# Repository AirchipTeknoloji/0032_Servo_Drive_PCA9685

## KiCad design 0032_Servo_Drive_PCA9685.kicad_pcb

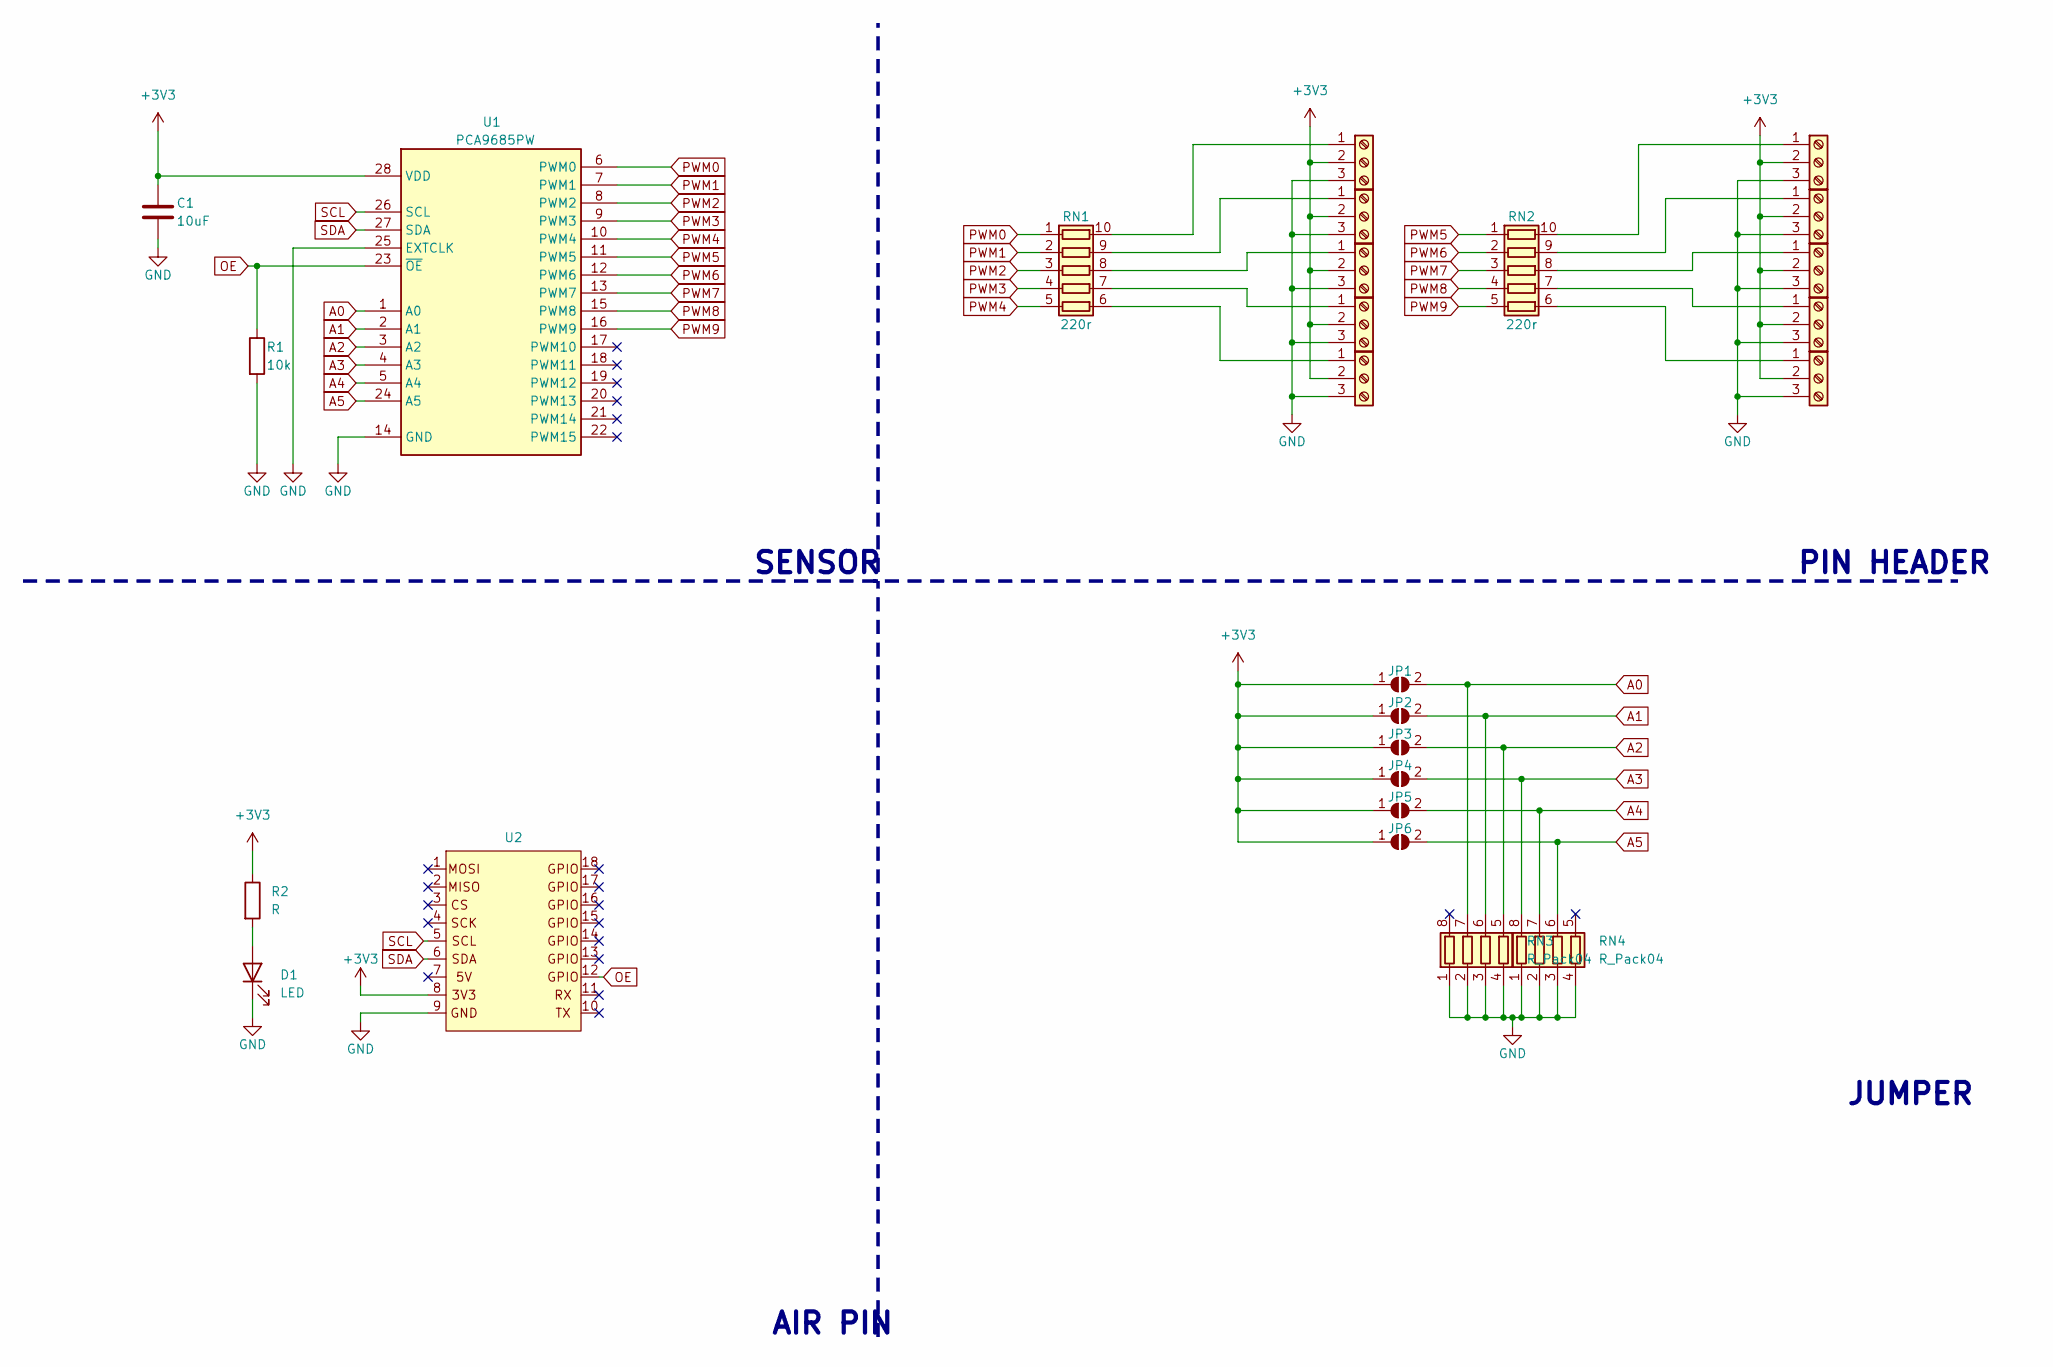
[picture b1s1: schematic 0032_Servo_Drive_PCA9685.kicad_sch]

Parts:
C1: 10uF; C_0603_1608Metric
D1: LED; LED_0603_1608Metric
J1, J2, J3, J4, J5, J6, J7, J8, J9, J10: Screw_Terminal_01x03; PinSocket_1x03_P2.54mm_Vertical
JP1, JP2, JP3, JP4, JP5: SolderJumper_2_Open; SolderJumper-2_P1.3mm_Open_RoundedPad1.0x1.5mm
JP6: ESolderJumper_2_Open; SolderJumper-2_P1.3mm_Open_RoundedPad1.0x1.5mm
R1: 10k; R_0603_1608Metric
R2: R; R_0603_1608Metric
RN1, RN2: 220r; R_Array_Convex_5x0603
RN3, RN4: R_Pack04; R_Array_Concave_4x0402
U1: PCA9685PW; TSSOP-28_4.4x9.7mm_P0.65mm
U2: pin_header_5-3

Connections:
+3V3: C1.1, J1.2, J2.2, J3.2, J4.2, J5.2, J6.2, J7.2, J8.2, J9.2, J10.2, JP1.1 (A), JP2.1 (A), JP3.1 (A), JP4.1 (A), JP5.1 (A), JP6.1 (A), R2.1, U1.28 (VDD), U2.8
A0: JP1.2 (B), RN3.7 (R2.2), U1.1 (A0)
A1: JP2.2 (B), RN3.6 (R3.2), U1.2 (A1)
A2: JP3.2 (B), RN3.5 (R4.2), U1.3 (A2)
A3: JP4.2 (B), RN4.8 (R1.2), U1.4 (A3)
A4: JP5.2 (B), RN4.7 (R2.2), U1.5 (A4)
A5: JP6.2 (B), RN4.6 (R3.2), U1.24 (A5)
GND: C1.2, D1.1 (K), J1.3, J2.3, J3.3, J4.3, J5.3, J6.3, J7.3, J8.3, J9.3, J10.3, R1.2, RN3.1 (R1.1), RN3.2 (R2.1), RN3.3 (R3.1), RN3.4 (R4.1), RN4.1 (R1.1), RN4.2 (R2.1), RN4.3 (R3.1), RN4.4 (R4.1), U1.14 (GND), U1.25 (EXTCLK), U2.9
unnamed: D1.2 (A), R2.2
unnamed: J1.1, RN1.10 (R1.2)
unnamed: J2.1, RN1.9 (R2.2)
unnamed: J3.1, RN1.8 (R3.2)
unnamed: J4.1, RN1.7 (R4.2)
unnamed: J5.1, RN1.6 (R5.2)
unnamed: J6.1, RN2.10 (R1.2)
unnamed: J7.1, RN2.9 (R2.2)
unnamed: J8.1, RN2.8 (R3.2)
unnamed: J9.1, RN2.7 (R4.2)
unnamed: J10.1, RN2.6 (R5.2)
OE: R1.1, U1.23 (~OE), U2.12
PWM0: RN1.1 (R1.1), U1.6 (PWM0)
PWM1: RN1.2 (R2.1), U1.7 (PWM1)
PWM2: RN1.3 (R3.1), U1.8 (PWM2)
PWM3: RN1.4 (R4.1), U1.9 (PWM3)
PWM4: RN1.5 (R5.1), U1.10 (PWM4)
PWM5: RN2.1 (R1.1), U1.11 (PWM5)
PWM6: RN2.2 (R2.1), U1.12 (PWM6)
PWM7: RN2.3 (R3.1), U1.13 (PWM7)
PWM8: RN2.4 (R4.1), U1.15 (PWM8)
PWM9: RN2.5 (R5.1), U1.16 (PWM9)
SCL: U1.26 (SCL), U2.5
SDA: U1.27 (SDA), U2.6

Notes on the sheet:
JUMPER
PIN HEADER
AIR PIN
SENSOR

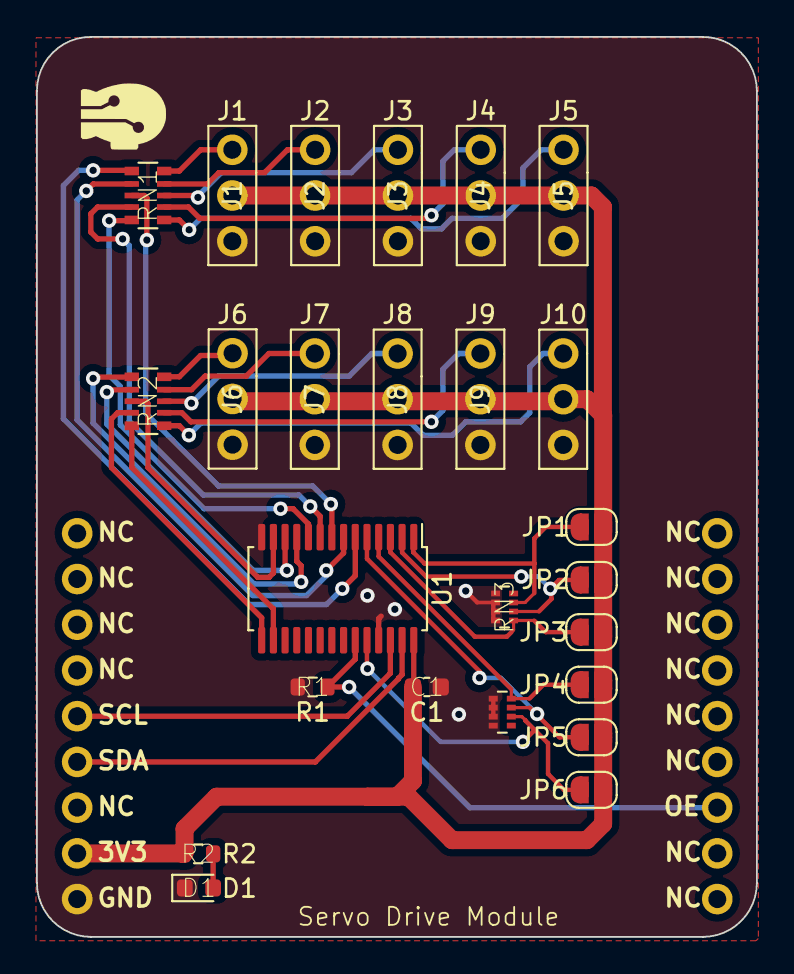
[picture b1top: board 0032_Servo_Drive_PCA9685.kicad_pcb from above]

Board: 2 copper layers, 40.0 x 50.0 mm, 26 parts (0 on the bottom side), 32 nets.
